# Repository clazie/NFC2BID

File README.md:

# NFC2BID

This project is based on a project from Rainer Kembügler ("onki") from  02. Dezember 2016 
(seen here: `https://onki.de/uebermich/bauberichte/289-bid2nfc-einbau-ins-ladegeraet <https://onki.de/uebermich/bauberichte/289-bid2nfc-einbau-ins-ladegeraet>`_ )

Information can also found here: `https://www.rc-network.de/threads/bid2nfc-als-nachr%C3%BCstl%C3%B6sung.587281/ <https://www.rc-network.de/threads/bid2nfc-als-nachr%C3%BCstl%C3%B6sung.587281/>`_

I collected all informations necessary to build it by my own and refactored the firmware for 
using it with PlatformIO.

# How to build PlatformIO based project

1. `Install PlatformIO Core <http://docs.platformio.org/page/core.html>`_
2. Download `development platform with examples <https://github.com/platformio/platform-atmelavr/archive/develop.zip>`_
3. Extract ZIP archive
4. Run these commands:

.. code-block:: bash

    # Change directory to example
    > cd platform-atmelavr/examples/arduino-blink

    # Build project
    > platformio run

    # Upload firmware
    > platformio run --target upload

    # Build specific environment
    > platformio run -e uno

    # Upload firmware for the specific environment
    > platformio run -e uno --target upload

    # Clean build files
    > platformio run --target clean

# Copyright PlatformIO
    Copyright 2014-present PlatformIO <contact@platformio.org>
    Licensed under the Apache License, Version 2.0 (the "License");
    you may not use this file except in compliance with the License.
    You may obtain a copy of the License at
       http://www.apache.org/licenses/LICENSE-2.0
    Unless required by applicable law or agreed to in writing, software
    distributed under the License is distributed on an "AS IS" BASIS,
    WITHOUT WARRANTIES OR CONDITIONS OF ANY KIND, either express or implied.
    See the License for the specific language governing permissions and
    limitations under the License.

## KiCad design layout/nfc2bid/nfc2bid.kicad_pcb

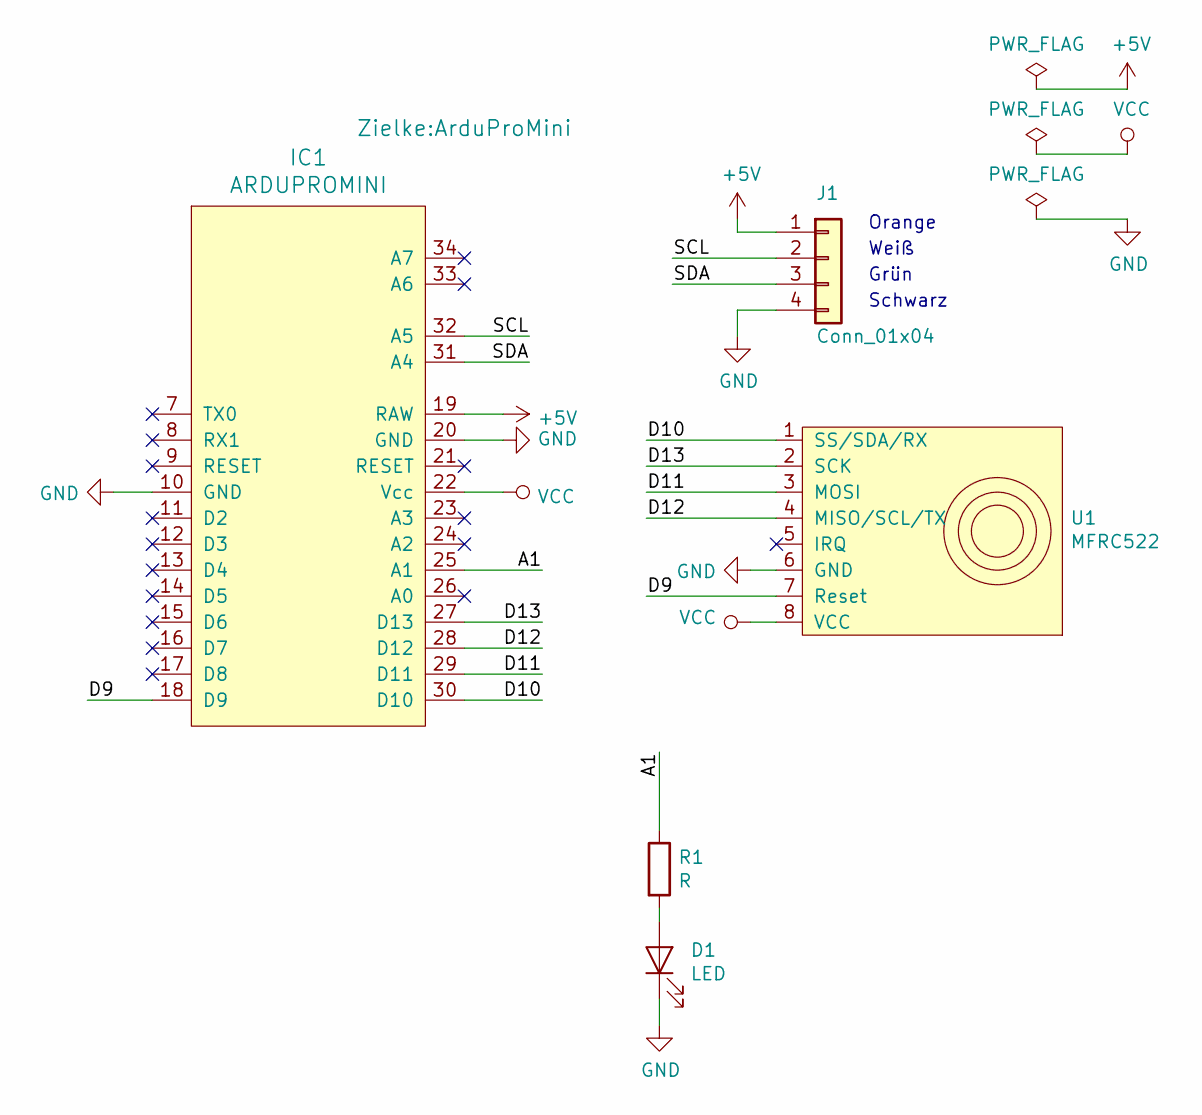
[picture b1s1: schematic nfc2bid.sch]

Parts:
D1: LED; LED_D3.0mm_Clear
IC1: ARDUPROMINI; ArduProMini
J1: Conn_01x04; PinHeader_1x04_P2.54mm_Horizontal
R1: R; R_Axial_DIN0309_L9.0mm_D3.2mm_P12.70mm_Horizontal
U1: MFRC522

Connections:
+5V: IC1.19 (RAW), J1.1
/A1: IC1.25 (A1), R1.1
/D9: IC1.18 (D9), U1.7 (Reset)
/D10: IC1.30 (D10), U1.1 (SS/SDA/RX)
/D11: IC1.29 (D11), U1.3 (MOSI)
/D12: IC1.28 (D12), U1.4 (MISO/SCL/TX)
/D13: IC1.27 (D13), U1.2 (SCK)
/SCL: IC1.32 (A5), J1.2
/SDA: IC1.31 (A4), J1.3
GND: D1.1 (K), IC1.10 (GND), IC1.20 (GND), J1.4, U1.6 (GND)
unnamed: D1.2 (A), R1.2
VCC: IC1.22 (Vcc), U1.8 (VCC)

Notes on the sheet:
Orange
Weiß
Grün
Schwarz

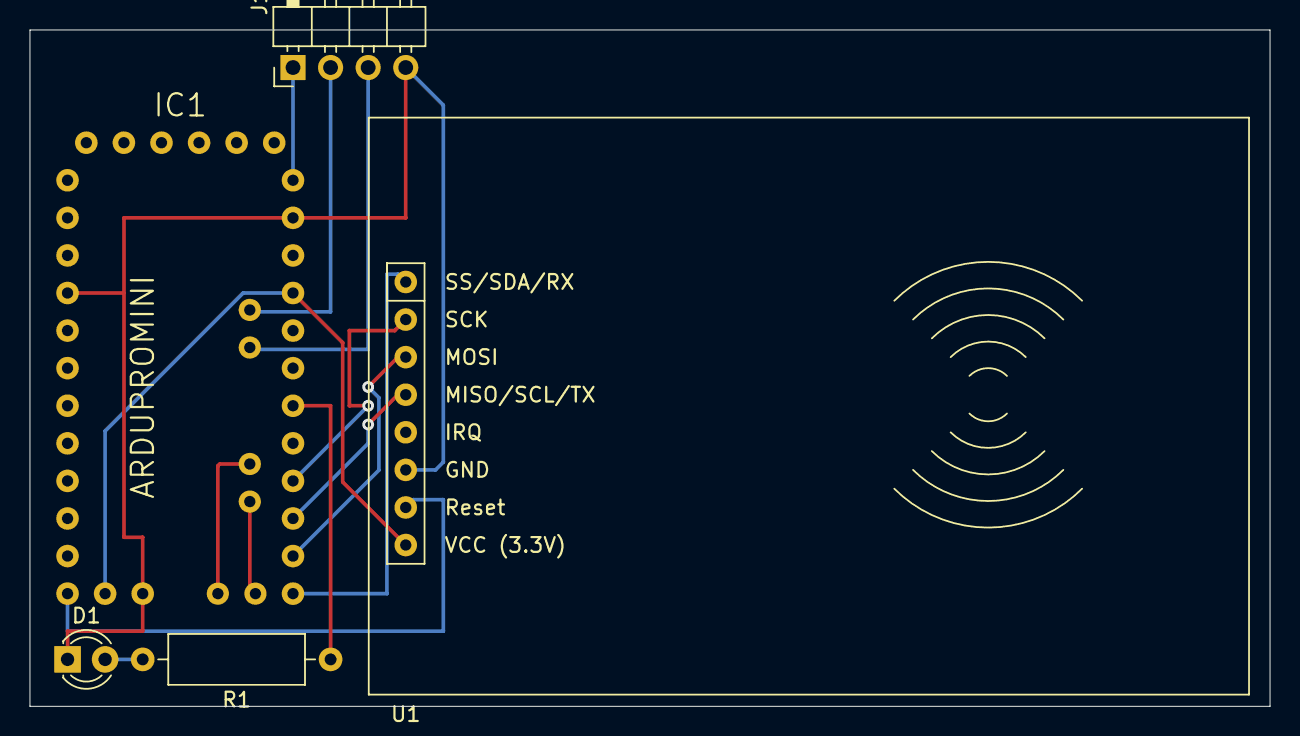
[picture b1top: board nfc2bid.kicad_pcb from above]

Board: 2 copper layers, 83.8 x 45.7 mm, 5 parts (0 on the bottom side), 12 nets.

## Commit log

2021-07-23 Initial checkin
2021-07-28 checkin nach backup
2021-07-28 Infos über RFID-Leser
2021-07-29 Gitignore angepasst
2021-07-29 MFRC522 Library korrigiert
2021-07-29 Docs Hardwarebeschreibung ergänzt
2021-07-29 Initial checkin Layout
2021-07-29 PlatformIO Build entfernt
2021-07-29 Refactoring für ProMini 3,3V 8MHz
2021-07-29 global.h erzeugt und Version eingefügt
2021-07-29 Readme mit Quellen ergänzt
2021-07-29 typo
2021-07-29 Print Version beim Start
2021-07-29 Deprecated env_default ersetzt
2021-07-29 Booleans korrigiert
2021-07-29 Kicad ProMini
2021-07-29 Fix zweite Karte lesen
2021-07-29 Infos für die BID Speicherstruktur
2021-07-29 Akkudaten Ausgabe
2021-07-29 Ausgabe Beispiel Serielle
2021-07-30 Github preparing
2021-07-30 Layoutentwurf
